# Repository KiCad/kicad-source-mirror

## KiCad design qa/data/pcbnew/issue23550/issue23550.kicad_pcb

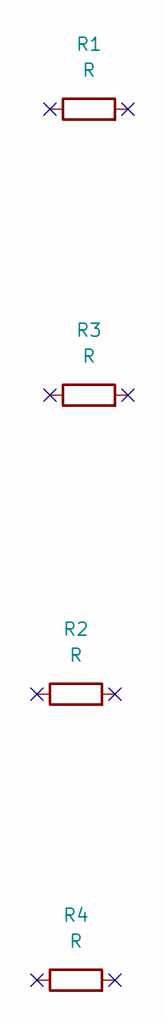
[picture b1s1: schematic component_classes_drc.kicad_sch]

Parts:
R1, R2, R3, R4: R; R_0603_1608Metric

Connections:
/Va_N: R1.2, R2.2
/Va_P: R1.1, R2.1
/Vb_N: R3.2, R4.2
/Vb_P: R3.1, R4.1

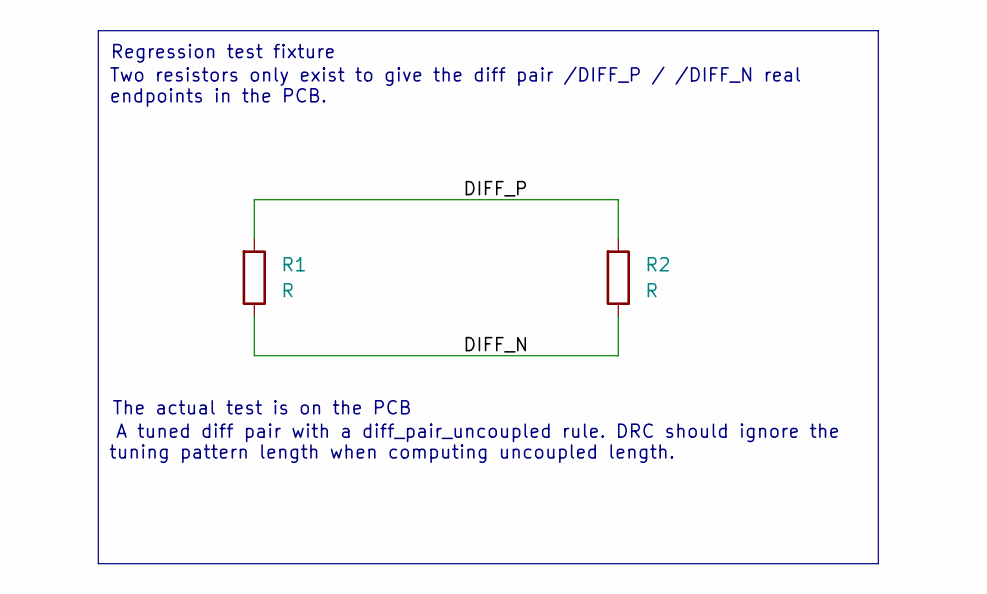
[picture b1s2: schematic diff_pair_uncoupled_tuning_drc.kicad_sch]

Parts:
R1, R2: R; R_0805_2012Metric

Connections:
/Va_N: R1.2, R2.2
/Va_P: R1.1, R2.1

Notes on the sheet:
Two resistors only exist to give the diff pair /DIFF_P / /DIFF_N real endpoints in the PCB.
The actual test is on the PCB
tuning pattern length when computing uncoupled length.
A tuned diff pair with a diff_pair_uncoupled rule. DRC should ignore the
Regression test fixture

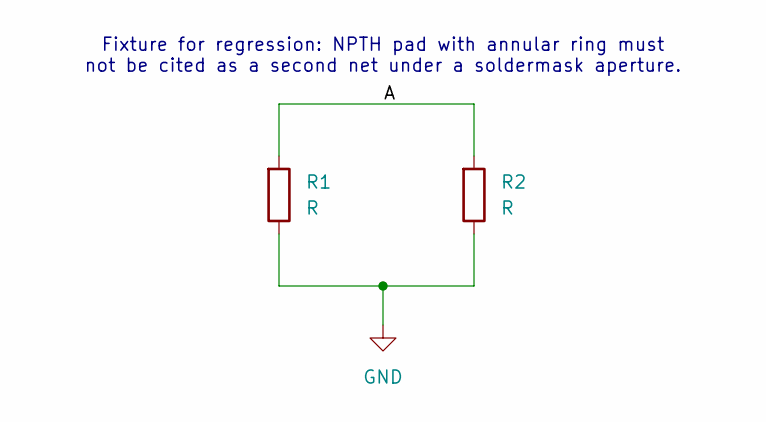
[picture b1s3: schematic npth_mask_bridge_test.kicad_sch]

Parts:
R1, R2: R; R_0805_2012Metric

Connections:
/Va_N: R1.2, R2.2
/Va_P: R1.1, R2.1

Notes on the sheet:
Fixture for regression: NPTH pad with annular ring must not be cited as a second net under a soldermask aperture.

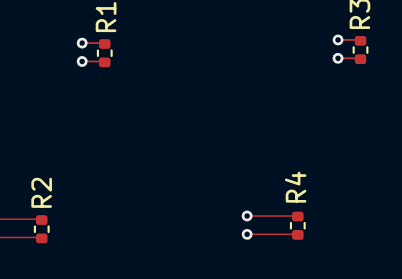
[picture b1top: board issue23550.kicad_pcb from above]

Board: 16 copper layers, 4 parts (0 on the bottom side), 4 nets.

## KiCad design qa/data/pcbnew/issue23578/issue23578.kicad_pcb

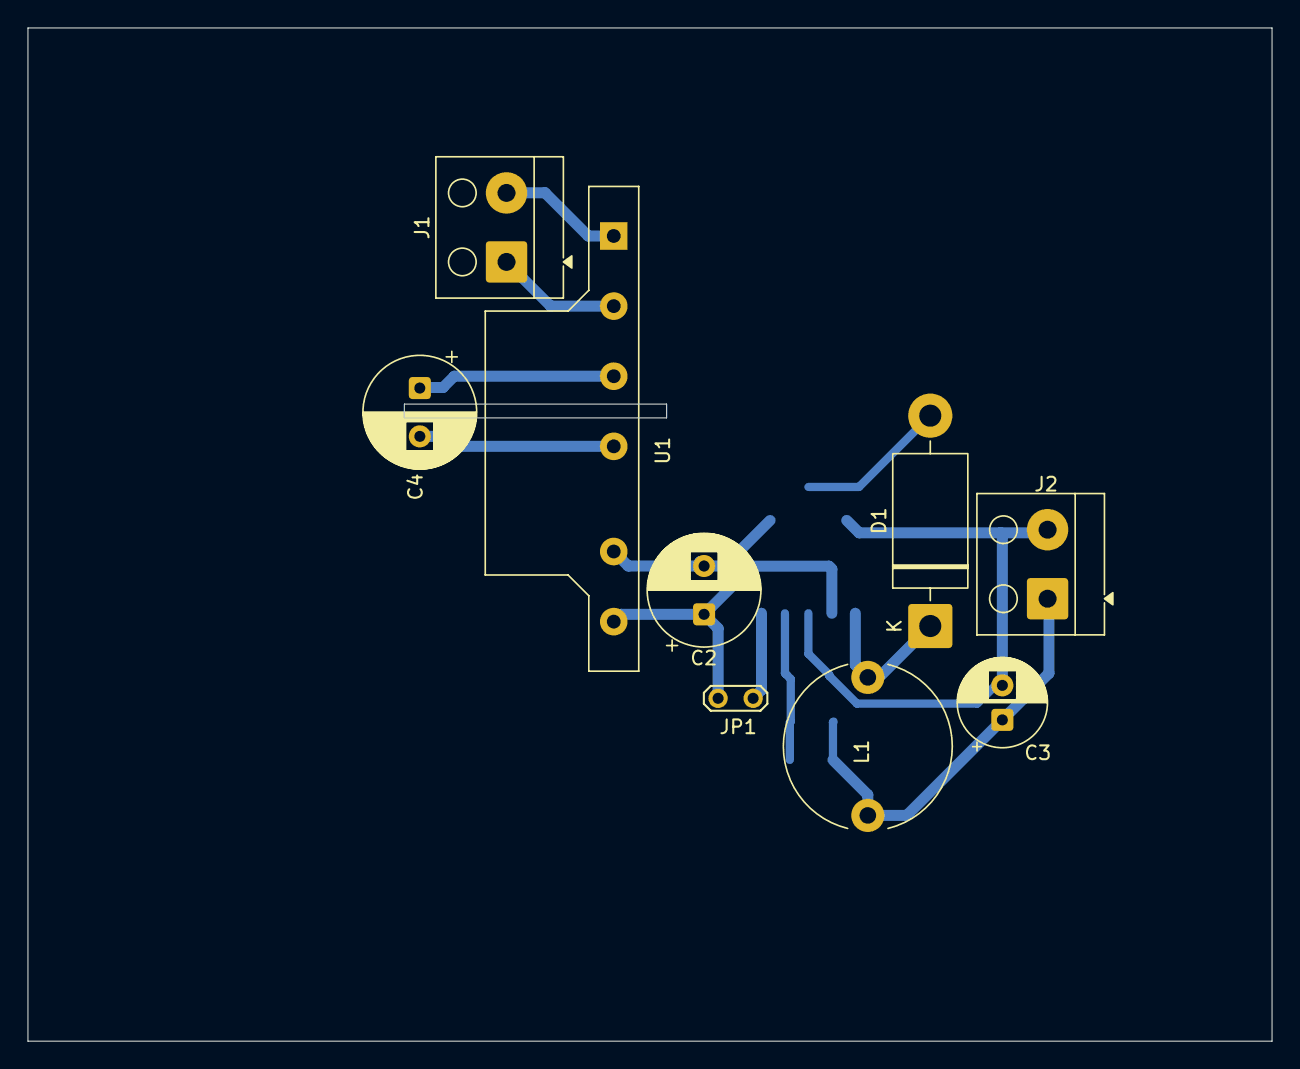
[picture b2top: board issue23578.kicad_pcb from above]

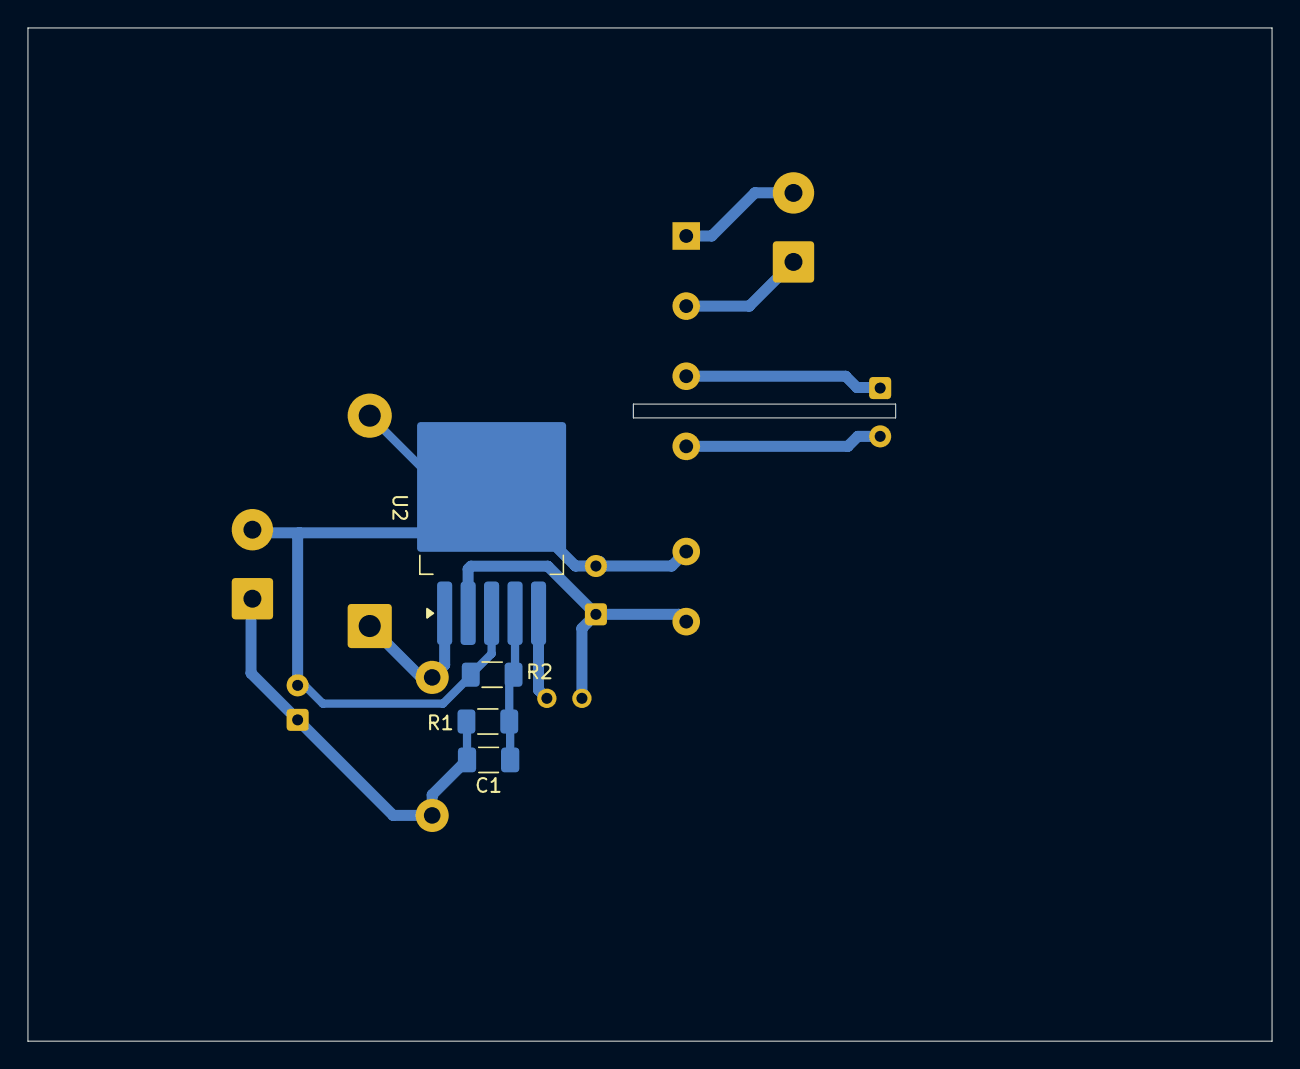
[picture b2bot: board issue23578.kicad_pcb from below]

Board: 2 copper layers, 90.1 x 73.4 mm, 13 parts (4 on the bottom side), 10 nets.

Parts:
C1: 6n8; C_1206_3216Metric_Pad1.33x1.80mm_HandSolder
C2: 100u/35V; CP_Radial_D8.0mm_P3.50mm
C3: 330u/6,3V; CP_Radial_D6.3mm_P2.50mm
C4: 10u/350V; CP_Radial_D8.0mm_P3.50mm
D1: 1N5822; D_DO-201AD_P15.24mm_Horizontal
J1: Vstup 230V; Altech_AK100_1x02_P5.00mm
J2: Vystup +1,8V; Altech_AK100_1x02_P5.00mm
JP1: Jumper_2_Bridged; TestPoint_2Pads_Pitch2.54mm_Drill0.8mm
L1: 150uH; L_Radial_D12.0mm_P10.00mm_Neosid_SD12_style1
R1: 470R; R_1206_3216Metric_Pad1.30x1.75mm_HandSolder
R2: 1k; R_1206_3216Metric_Pad1.30x1.75mm_HandSolder
U1: PBO-3-S24; Converter_ACDC_CUI_PBO-3-Sxx_THT_Vertical
U2: LM2595S-ADJ; TO-263-5_TabPin3

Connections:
+1V8: C1.2, C3.1, J2.1, L1.2, R1.1
GND: C2.2, C3.2, D1.2 (A), J2.2, R2.1, U1.10 (-Vo), U2.3 (GND)
unnamed: D1.1 (K), L1.1, U2.1 (OUT)
unnamed: J1.1, U1.3 (AC(L))
unnamed: J1.2, U1.1 (AC(N))
unnamed: JP1.1 (A), U2.5 (ON/~OFF)
unnamed: C2.1, JP1.2 (B), U1.12 (+Vo), U2.2 (VIN)
unnamed: C4.1, U1.5 (+V(CAP))
unnamed: C4.2, U1.7 (-V(CAP))
unnamed: C1.1, R1.2, R2.2, U2.4 (FB)
